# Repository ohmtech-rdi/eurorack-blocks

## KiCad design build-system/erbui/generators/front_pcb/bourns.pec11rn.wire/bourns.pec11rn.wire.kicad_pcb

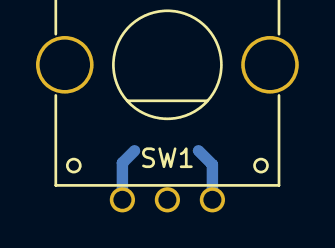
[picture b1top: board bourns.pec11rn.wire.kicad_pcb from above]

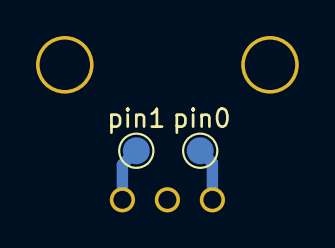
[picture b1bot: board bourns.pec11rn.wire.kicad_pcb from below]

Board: 2 copper layers, 3 parts (2 on the bottom side), 2 nets.

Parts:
SW1: RotaryEncoder; PEC11R-4220F-N0024
TP1, TP2: TestPoint; TestPoint_Pad_D1.5mm

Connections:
Pin0: SW1.A, TP1.1
Pin1: SW1.B, TP2.1
